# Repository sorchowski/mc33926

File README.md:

A wrapping class to operate a MC33926 motor driver.

[Pololu Single Driver](https://www.pololu.com/product/1212)<br>
[Pololu Dual Driver](https://www.pololu.com/product/1213)<br>
[MC33926 Datasheet](https://pololu.com/file/0J233/MC33926.pdf)

# How to Use

## Setup and Set Speed

```
    #include <MC33926>

    #define IN1_PIN 6
    #define IN2_PIN 9

    MC33926 motorController(IN1_PIN, IN2_PIN);

    motorController.setSpeed(100);
```

## Current Sense 

Set the pin on which to read current sense values.

`void setCurrentSensePin(int fbCurrentSensePin, float referenceVoltage)`

Returns a float value representing the current in milliamps.

`float getCurrent()`

Note, this feature is currently untested.

## Status Flag

You can actively read the status flag sense pin at-will or register an interrupt handler to execute upon a status change event. Either must be invoked at setup time.

`void registerStatusChangeHandler(void (*statusServiceRoutine)(void), int statusFlagPin)`

`void setStatusFlagPin(int statusFlagPin)`

Returns true if the mc33926 has set the status flag.

`boolean getStatus()`

# Expected Logic Connections

3.3v or 5v is allowed. All values below are based on 5v

## Input Pins (to MC33926)
|Pin  | Level |
|:---:|:-----:|
|VDD  |5v     |
|EN   |5v     |
|D1   |0v     |
|D2   |5v     |
|INV  |0v     |
|SLEW |0v for low freq pwm, 5v for high freq pwm|
|IN1 (fwd)|PWM    |
|IN2 (fwd)|0v     |
|IN1 (reverse)|0v     |
|IN2 (reverse)|PWM    |

For the Dual MC33926 VDD, EN, INV, and SLEW cover both controllers. D1, D2 and IN1, IN2 are duplicated.

## Output Pins (from MC33926)
|Pin  | Level |
|:---:|:-----:|
|FB   |0v w/ pull-down resistor (analog)|
|SF   |5v w/ pull-up resistor (digital) |

# Arduino Pin Information

Uno pwm pins:

3, 5, 6, 9, 10, 11, 490 Hz (pins 5 and 6: 980 Hz)

Due pwm pins:

2-13, 1000 Hz

use analogWriteResolution to set higher resolution. i.e. "12" for 12-bit -> 4096bit resolution

pins DAC0 and DAC1 are "true" analog

# MC33926 Breakout

The dual MC33926 board has a large number of configuration pins. Many of these are easily set using a jumper with the onboard VDD or GND connections. But other optional configurations can require a large number of VDD or GND connections.

This [dual breakout board](schematics) provides eight VDD and eight GND connections for various settings. The board also provides connections for a four-wire ribbon cable to the dual IN1 and IN2 connections.

[Breakout Board](docs/mc33926_breakout1.jpg)

[Example implementation](docs/mc33926_breakout2.jpg)

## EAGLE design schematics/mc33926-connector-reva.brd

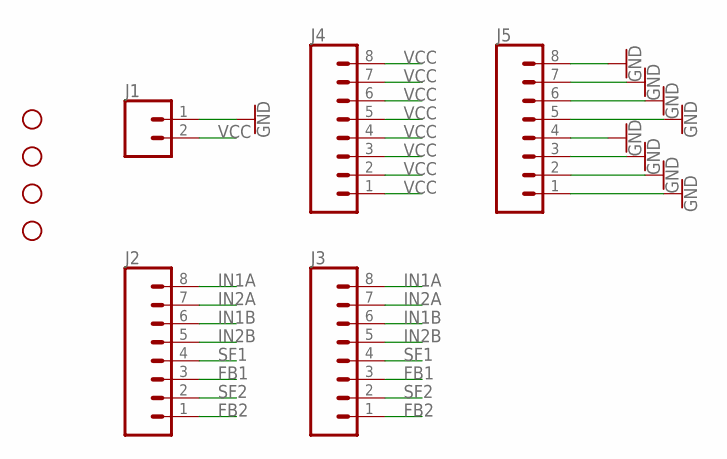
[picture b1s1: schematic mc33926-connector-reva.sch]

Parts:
H1, H2, H3, H4: STAND-OFF
J1: CONN_02-JST-2MM-SMT; JST-2-SMD
J2, J3, J4, J5: CONN_08"; 1X08

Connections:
FB1: J2.3, J3.3
FB2: J2.1, J3.1
GND: J1.1 (2), J5.1, J5.2, J5.3, J5.4, J5.5, J5.6, J5.7, J5.8
IN1A: J2.8, J3.8
IN1B: J2.6, J3.6
IN2A: J2.7, J3.7
IN2B: J2.5, J3.5
SF1: J2.4, J3.4
SF2: J2.2, J3.2
VCC: J1.2 (1), J4.1, J4.2, J4.3, J4.4, J4.5, J4.6, J4.7, J4.8

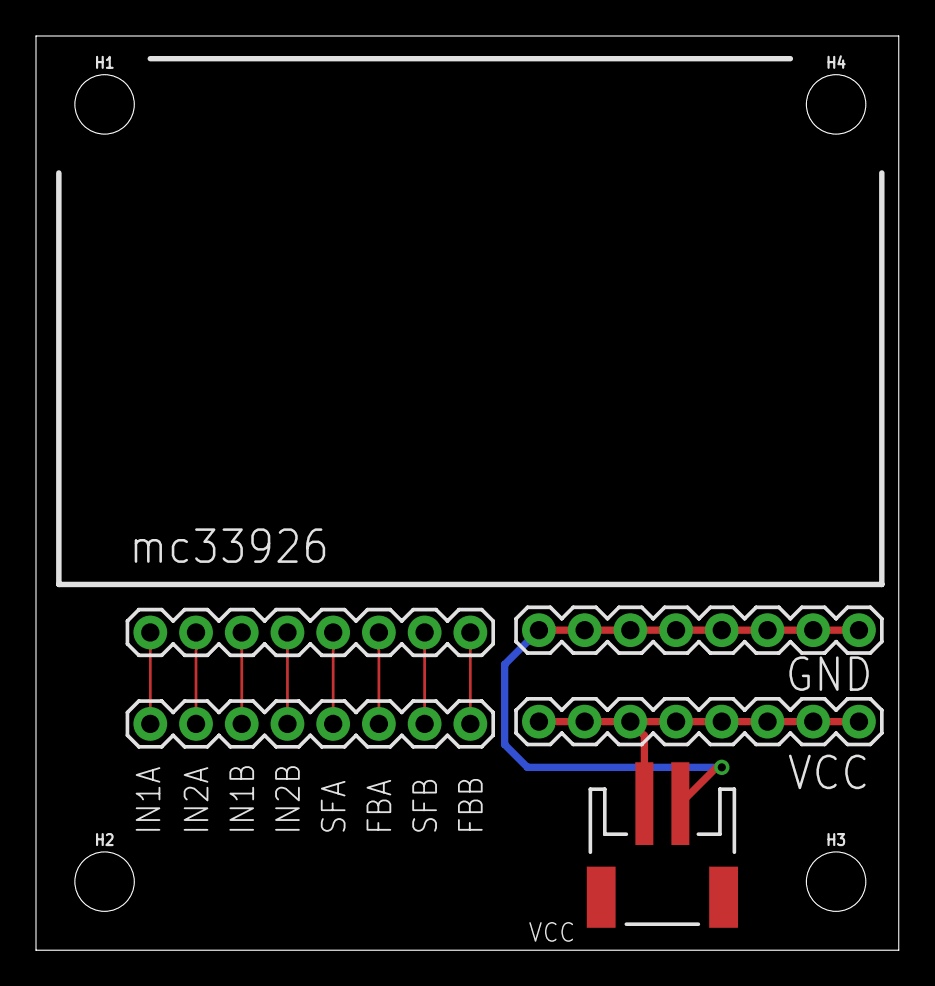
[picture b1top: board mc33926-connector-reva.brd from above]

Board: 2 copper layers, 47.9 x 50.8 mm, 9 parts (0 on the bottom side), 10 nets.

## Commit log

2023-02-04 move files from ArduinoLibs to separate repo
2023-02-27 Remove datasheet
2023-02-27 images
2023-02-27 fix readme
2023-09-19 Add support for analogWriteResolution for Due
2023-11-26 add schematic image

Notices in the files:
parts and their libraries:
SparkFun-Hardware: Licensing: Creative Commons ShareAlike 4.0 International - https://creativecommons.org/licenses/by-sa/4.0
